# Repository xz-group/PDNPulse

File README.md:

# PDNPulse

The PDNPulse project is a power delivery network (PDN) based PCB anomaly detection framework that can identify a wide spectrum of board-level malicious modifications.

This repository contains the source files and guidance for using the PDNPulse framework.

## In this repository

* `probe/` - The source files and guide for [our custom probe](./probe/README.md)

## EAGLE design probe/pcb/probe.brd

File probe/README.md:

# PDNPulse Probe

PDNPulse Probe is our custom probe for the PDNPulse project. 
In this folder you will find the source files (Eagle PCB design files and STL files for 3D printing) for the probe.
This document will guide you through the process of building the probe.

## Features of the probe
+ Low cost
+ Accurate
+ Flexible adjustment of the distance between the probe tips
    >This is the main motivation why we want to build our own probe. The probe tips are adjustable using a screw driver. This is useful when we want to attached the probe to a PCB. We can adjust the distance between the probe tips to match the distance between the pads on the PCB without replacing the probes. This is not possible on the commercial probes.

## How to USE the probe
+ Connect the probe to Vector Network Analyzer (VNA) using the SMA connector
+ Connect the probe to a positioner or holder using the screw and nut
+ Adjust the distance between the probe tips using the screw driver (M2)

## How to BUILD the probe

There are two parts to the probe: the PCB and the mechanical tuner. The PCB is the main part of the probe and contains the circuitry for the probe. The mechanical tuner is used to adjust the distance between the probe tips.

### 0. What you need
+ Test probes with springs (x2). We bought ours from Taobao. Ours are 0.5mm in diameter and 16mm in length (13mm for the tip and 3mm for the spring). There are similar ones on [Amazon](https://www.amazon.com/uxcell-Spherical-Radius-Spring-Probes/dp/B007Q8JILQ/ref=asc_df_B007Q8JILQ/?tag=hyprod-20&linkCode=df0&hvadid=416668650463&hvpos=&hvnetw=g&hvrand=1946963476250155027&hvpone=&hvptwo=&hvqmt=&hvdev=c&hvdvcmdl=&hvlocint=&hvlocphy=9022867&hvtargid=pla-833155082360&psc=1&tag=&ref=&adgrpid=90730998421&hvpone=&hvptwo=&hvadid=416668650463&hvpos=&hvnetw=g&hvrand=1946963476250155027&hvqmt=&hvdev=c&hvdvcmdl=&hvlocint=&hvlocphy=9022867&hvtargid=pla-833155082360).

+ Edge mount SMA connector (x1).

+ M2 screws, nuts and washers:
    + M2x6 screws (x1)
    + M2x12 screws (x2)
    + M2 nuts (x3)
    + M2 washers (x7)

### 1. Fabricate the PCB and 3D print the mechanical tuner

+ The PCB is designed in `Eagle CAD`. You can find the source files in the `pcb` folder. We used [JLCPCB](https://jlcpcb.com/) for our fabrication.
The PCB layout is shown below:

+ 3D print the mechanical tuner using the STL files in the `mechanical_tuner` folder. There are three parts: the base, the left and right arms. *Print the parts with the finest resolution possible.* The mechanical tuner is shown below (gray parts):

### 2. Assemble the PCB

+ Solder the SMA connector to the PCB
+ Solder the two probe tips to the PCB (the bottom side of the PCB labeled as `GND` and `S`). You should solder the tips such that they align with the marks on the PCB.

### 3. Assemble the mechanical tuner

The mechanism of the tuner is that it builds a "seazor" like structure. The base is fixed to the PCB and the left and right arms are connected to the base using the screws and nuts. The distance between the probe tips is adjusted by moving the left and right arms.

To assemble the tuner, follow the steps below:

+ Stick the base to the PCB using the hot glue gun. Make sure the base is aligned with the marks on the PCB.

+ Put one `M2 Nut` on Position `1`, two `M2 Washers` on Position `3` and two `M2 Washers` on Position `5`. 

+ Put one `M2x12 Screw` on Position `2` and one `M2x12 Screw` on Position `4`. 

+ Put one `M2 Nut` on Position `6` of the left arm and one `M2 Nut` on Position `6` of the right arm.

+ Put left arm and right arm on the base. Make sure the two screws are inserted into the nuts on the arms.

+ Adjust the distance between the left and right arms and tighten the arms using the `M2x6 Screw` + `M2 Washers` and `M2 Nut` on Position `1`.

+ Finally, put the two probe tips into the two holes on the left and right arms.

> Note: You may want to use hot glue to fix some parts of the tuner to make it more stable.

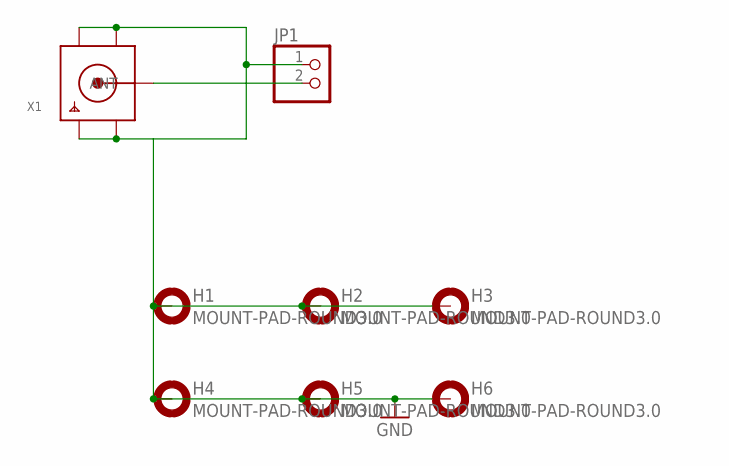
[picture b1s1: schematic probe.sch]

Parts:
H1, H2, H3, H4, H5, H6: MOUNT-PAD-ROUND3.0; 3,0-PAD
JP1: TIP-1X2; TIP-15
X1: SMACONNECTOR_EDGE_UFL; SMA_EDGELAUNCH_UFL

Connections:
GND: H1.B3,0, H2.B3,0, H3.B3,0, H4.B3,0, H5.B3,0, H6.B3,0, JP1.1, X1.GND@1 (GND1), X1.GND@2 (GND2), X1.GND@3 (GND3), X1.GND@4 (GND4)
unnamed: JP1.2, X1.P (ANT)

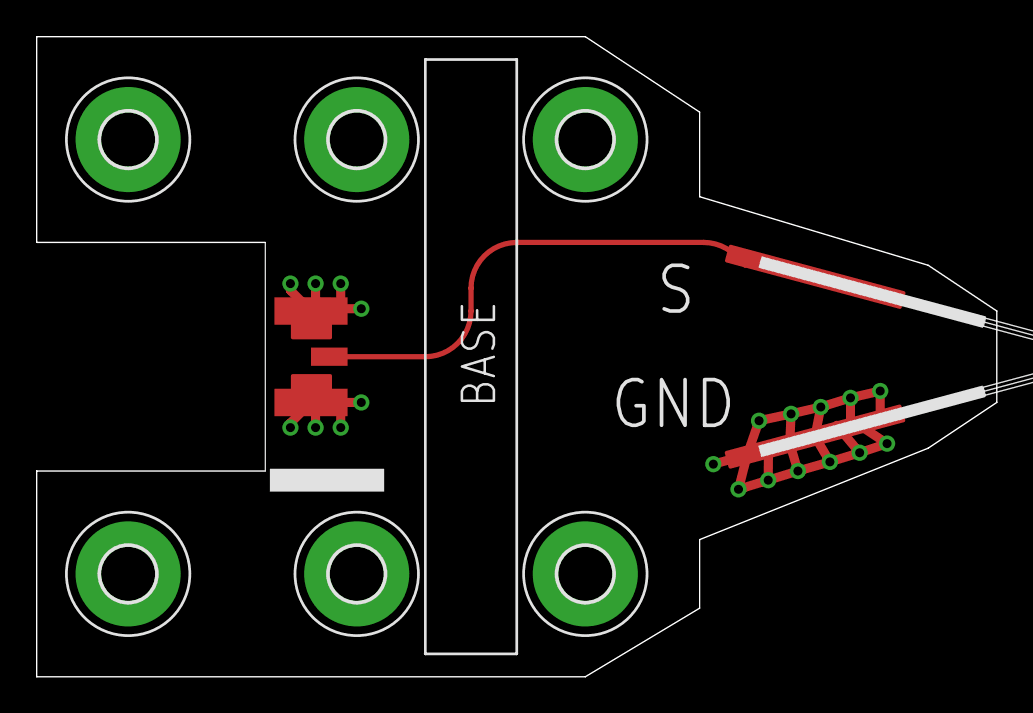
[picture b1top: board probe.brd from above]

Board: 4 copper layers, 53.3 x 35.6 mm, 8 parts (0 on the bottom side), 2 nets.

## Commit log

2023-01-18 Initial

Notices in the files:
parts and their libraries:
SparkFun-Aesthetics: Licensing: Creative Commons ShareAlike 4.0 International - https://creativecommons.org/licenses/by-sa/4.0
